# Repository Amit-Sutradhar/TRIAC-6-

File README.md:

# TRIAC-6-
TRIAC-Based AC Load Control Board
This board is a multi-channel TRIAC driver module designed for controlling AC loads such as motors, heaters, lamps, solenoid valves, and other mains-powered devices. It is suitable for industrial, IoT, and automation applications where reliable AC switching and isolation are required.
Key Features
Multiple TRIAC channels for independent control of AC loads
Opto-isolated gate driving for safety and noise immunity
Supports AC voltage up to 230–240V (can be adapted for higher ratings with proper TRIACs)
Through-hole TRIAC packages (TO-220) for easy replacement and heat-sink mounting
On-board snubber and gate resistors for stable TRIAC triggering
Screw terminal connectors for secure AC load connections
Compact and modular PCB layout for easy integration
Working Principle 

Each channel uses:
An opto-coupler to electrically isolate the low-voltage control side (MCU/logic) from the high-voltage AC side
A TRIAC that acts as a bidirectional AC switch
When a logic signal is applied to the opto-coupler, it triggers the TRIAC gate
The TRIAC then conducts current during the AC cycle and turns OFF automatically at the zero-crossing when the gate signal is removed
This makes the circuit simple, robust, and ideal for on/off AC control.
Applications
AC motor ON/OFF control
Heater and temperature control systems
Industrial automation panels
Smart power distribution units
IoT-based energy and appliance control[Uploading fp-info-cache…]()

Home automation (fans, lights, pumps)
Advantages
Electrical isolation improves safety and MCU protection
No mechanical wear (unlike relays)
Silent operation
Long operational life
Suitable for harsh electrical environments
Notes for Future Improvements
Heat sinks should be used for high-current loads
Zero-cross opto-couplers can be added for reduced EMI
PCB creepage and clearance should follow mains safety standards
Can be extended with current sensing or leakage detection

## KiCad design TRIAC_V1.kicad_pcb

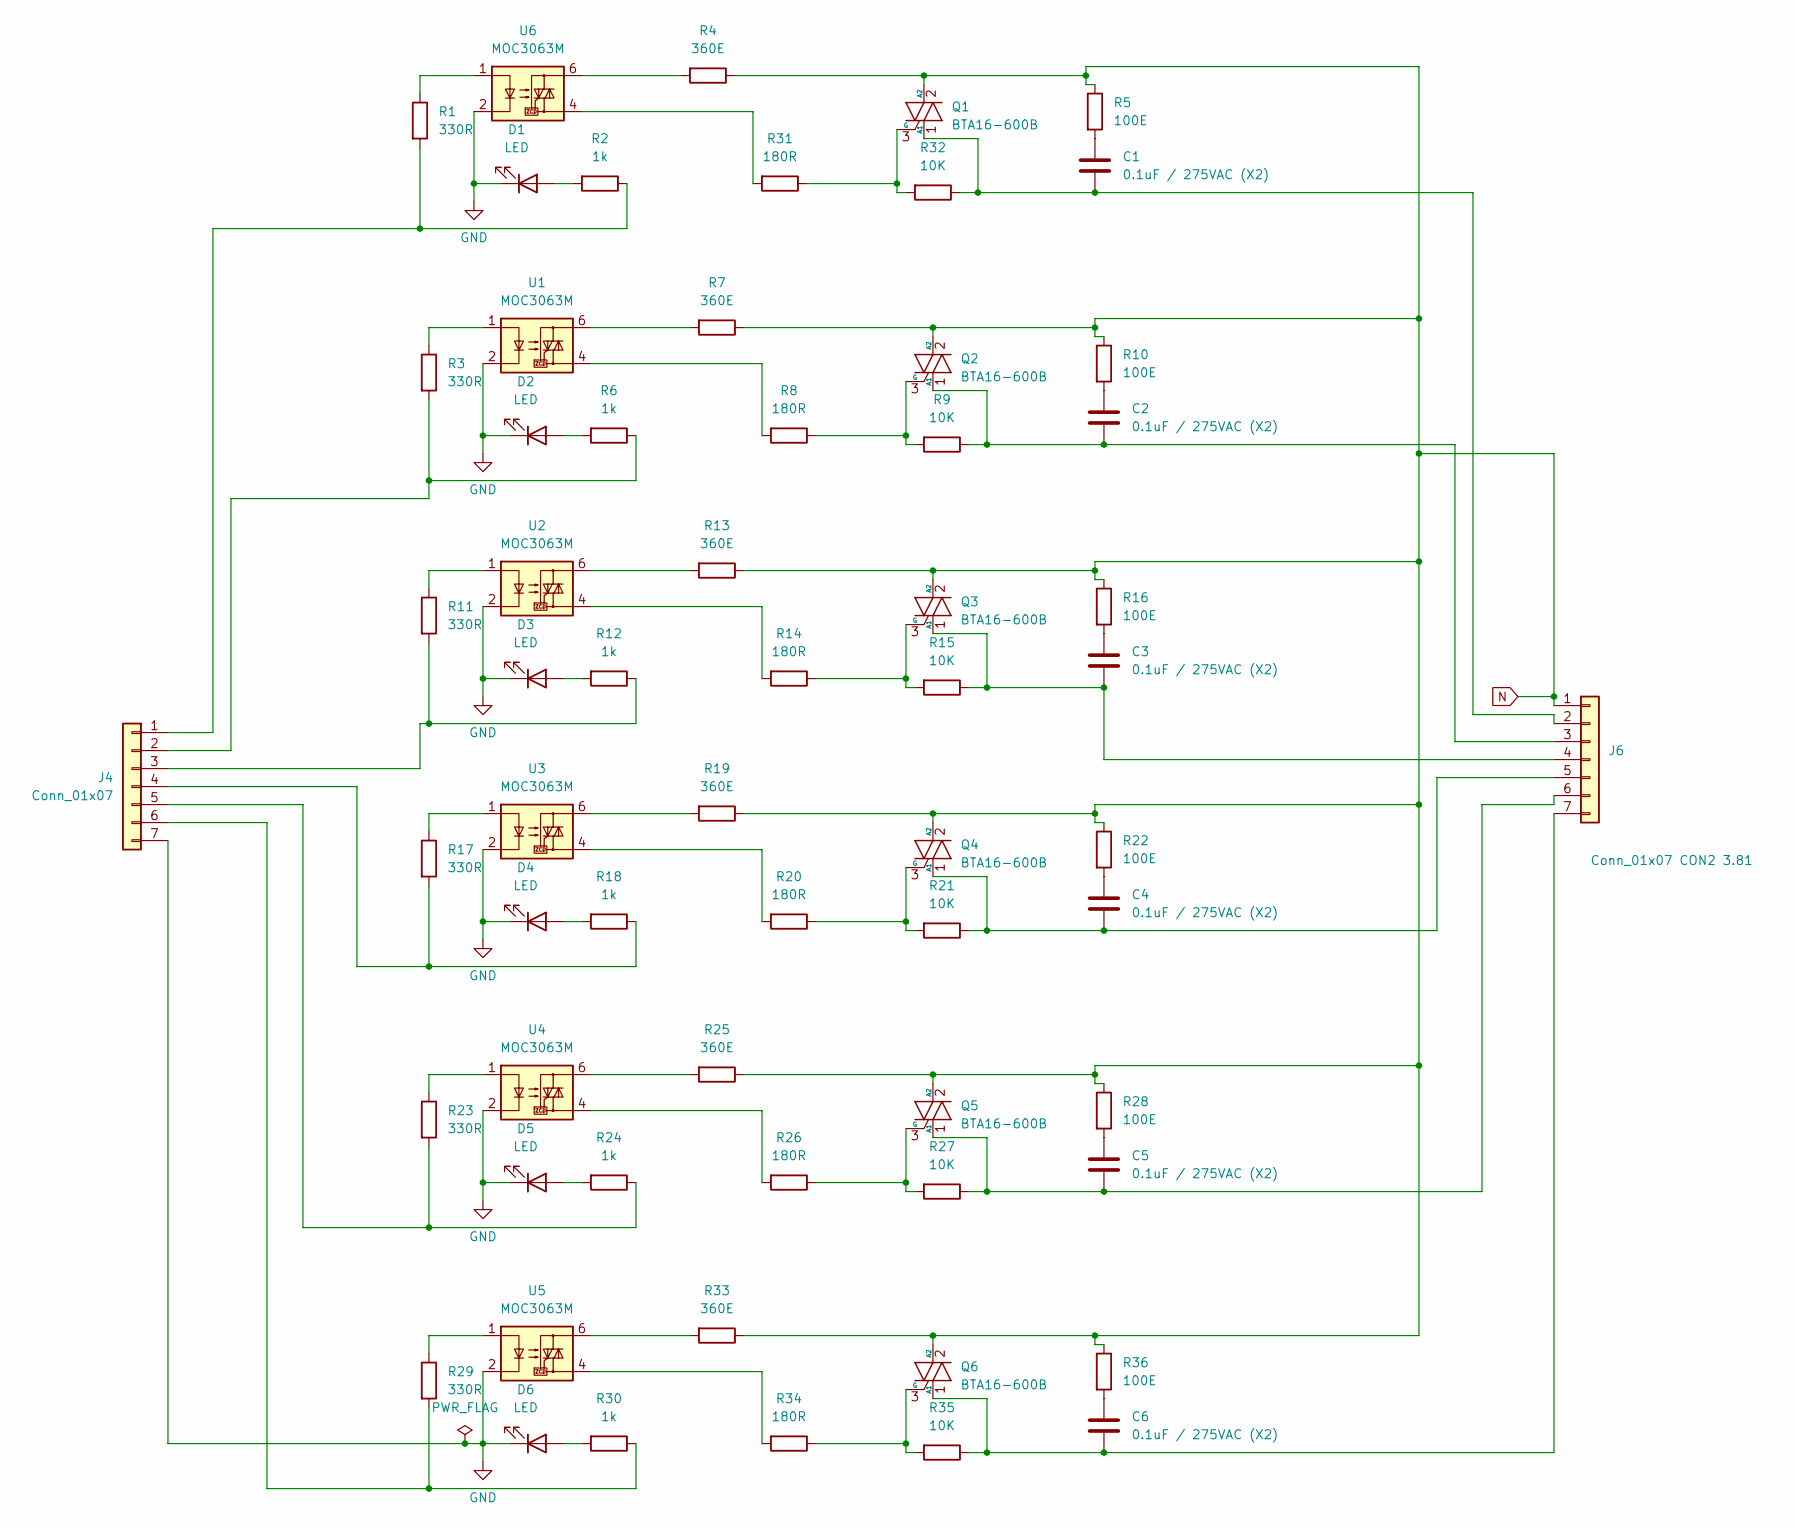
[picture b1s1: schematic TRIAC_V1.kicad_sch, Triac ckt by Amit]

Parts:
C1, C2, C3, C4, C5, C6: 0.1uF / 275VAC (X2); C_Rect_L13.0mm_W5.0mm_P10.00mm_FKS3_FKP3_MKS4
D1, D2, D3, D4, D5, D6: LED; LED_0805_2012Metric_Pad1.15x1.40mm_HandSolder
J4: Conn_01x07; TerminalBlock_Phoenix_MKDS-1-7-3.81_1x07_P3.81mm_Horizontal
J6: Conn_01x07 CON2 3.81; TerminalBlock_Phoenix_MKDS-1,5-7-5.08_1x07_P5.08mm_Horizont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
Q1, Q2, Q3, Q4, Q5, Q6: BTA16-600B; TO-220-3_Vertical
R1, R3, R11, R17, R23, R29: 330R; R_Axial_DIN0207_L6.3mm_D2.5mm_P7.62mm_Horizontal
R2, R6, R12, R18, R24, R30: 1k; R_Axial_DIN0207_L6.3mm_D2.5mm_P7.62mm_Horizontal
R4, R7, R13, R19, R25, R33: 360E; R_Axial_DIN0207_L6.3mm_D2.5mm_P7.62mm_Horizontal
R5, R10, R16, R22, R28, R36: 100E; R_Axial_DIN0411_L9.9mm_D3.6mm_P12.70mm_Horizontal
R8, R14, R20, R26, R31, R34: 180R; R_Axial_DIN0207_L6.3mm_D2.5mm_P7.62mm_Horizontal
R9, R15, R21, R27, R32, R35: 10K; R_Axial_DIN0207_L6.3mm_D2.5mm_P7.62mm_Horizontal
U1, U2, U3, U4, U5, U6: MOC3063M; DIP-6_W7.62mm

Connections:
GND: D1.1 (K), D2.1 (K), D3.1 (K), D4.1 (K), D5.1 (K), D6.1 (K), J4.7, U1.2, U2.2, U3.2, U4.2, U5.2, U6.2
N: J6.1, Q1.2 (A2), Q2.2 (A2), Q3.2 (A2), Q4.2 (A2), Q5.2 (A2), Q6.2 (A2), R4.1, R5.1, R7.1, R10.1, R13.1, R16.1, R19.1, R22.1, R25.1, R28.1, R33.1, R36.1
unnamed: C1.1, R5.2
unnamed: C2.1, R10.2
unnamed: C3.1, R16.2
unnamed: C4.1, R22.2
unnamed: C5.1, R28.2
unnamed: C6.1, R36.2
unnamed: D1.2 (A), R2.2
unnamed: D2.2 (A), R6.2
unnamed: D3.2 (A), R12.2
unnamed: D4.2 (A), R18.2
unnamed: D5.2 (A), R24.2
unnamed: D6.2 (A), R30.2
unnamed: J4.1, R1.2, R2.1
unnamed: J4.2, R3.2, R6.1
unnamed: J4.3, R11.2, R12.1
unnamed: J4.4, R17.2, R18.1
unnamed: J4.5, R23.2, R24.1
unnamed: J4.6, R29.2, R30.1
unnamed: C1.2, J6.2, Q1.1 (A1), R32.1
unnamed: C2.2, J6.3, Q2.1 (A1), R9.1
unnamed: C3.2, J6.4, Q3.1 (A1), R15.1
unnamed: C4.2, J6.5, Q4.1 (A1), R21.1
unnamed: C5.2, J6.6, Q5.1 (A1), R27.1
unnamed: C6.2, J6.7, Q6.1 (A1), R35.1
unnamed: Q1.3 (G), R31.1, R32.2
unnamed: Q2.3 (G), R8.1, R9.2
unnamed: Q3.3 (G), R14.1, R15.2
unnamed: Q4.3 (G), R20.1, R21.2
unnamed: Q5.3 (G), R26.1, R27.2
unnamed: Q6.3 (G), R34.1, R35.2
unnamed: R1.1, U6.1
unnamed: R3.1, U1.1
unnamed: R4.2, U6.6
unnamed: R7.2, U1.6
unnamed: R8.2, U1.4
unnamed: R11.1, U2.1
unnamed: R13.2, U2.6
unnamed: R14.2, U2.4
unnamed: R17.1, U3.1
unnamed: R19.2, U3.6
unnamed: R20.2, U3.4
unnamed: R23.1, U4.1
unnamed: R25.2, U4.6
unnamed: R26.2, U4.4
unnamed: R29.1, U5.1
unnamed: R31.2, U6.4
unnamed: R33.2, U5.6
unnamed: R34.2, U5.4

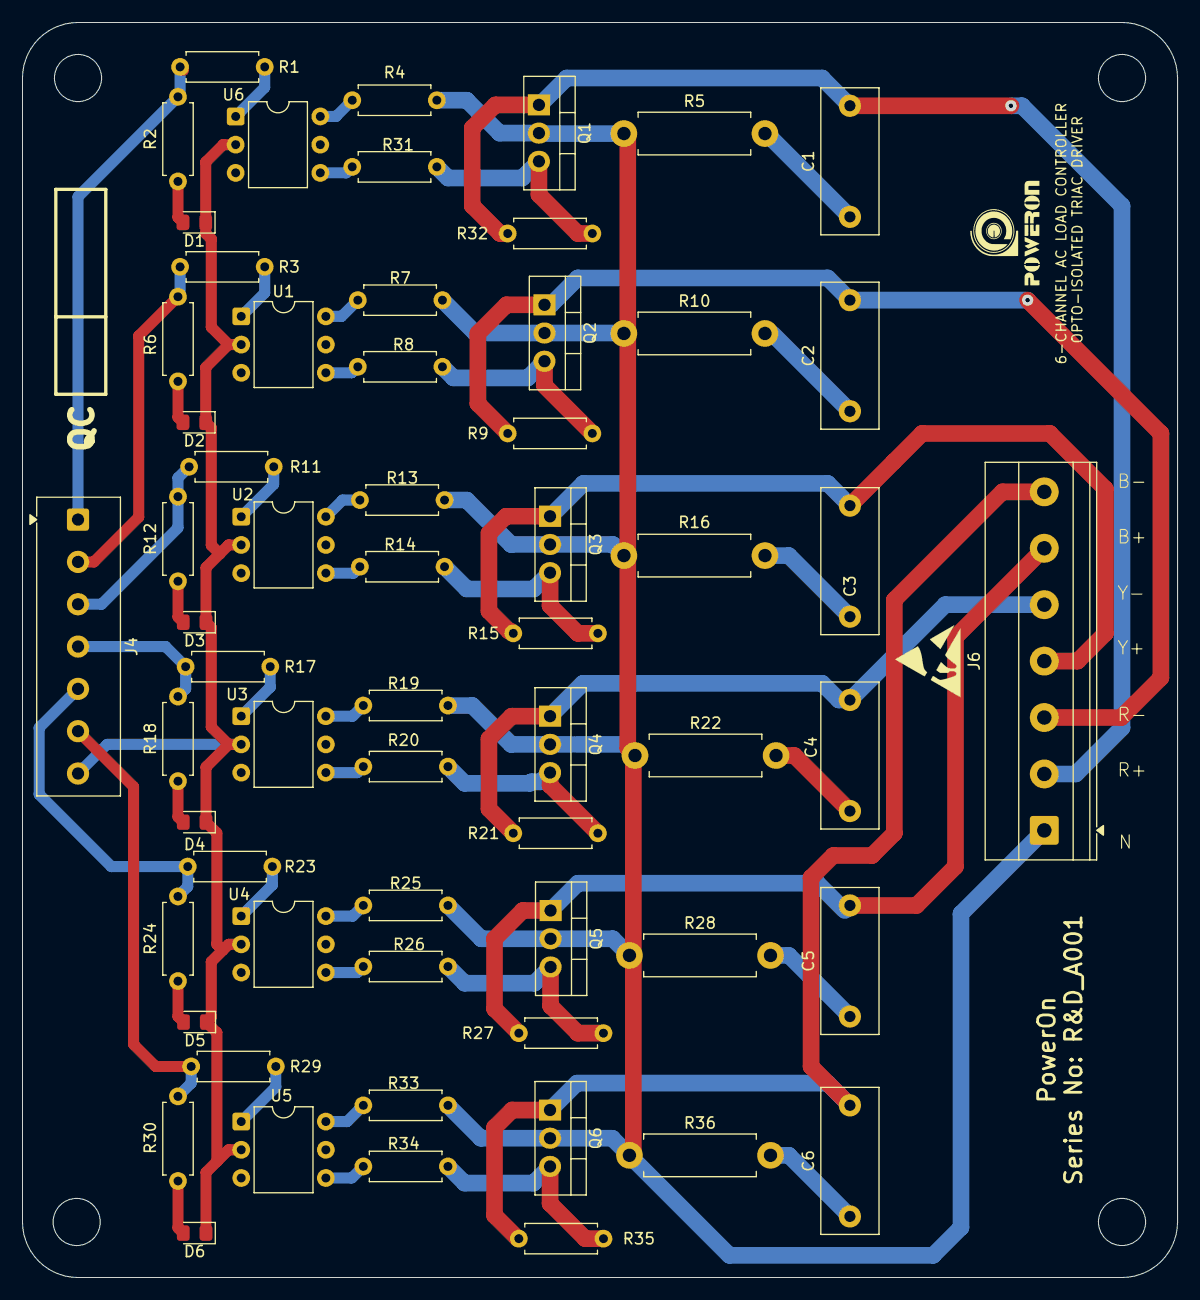
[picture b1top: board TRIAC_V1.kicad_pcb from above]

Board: 2 copper layers, 104.0 x 113.0 mm, 62 parts (0 on the bottom side), 50 nets.

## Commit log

2026-01-15 Fix link formatting in IoT-based control section
